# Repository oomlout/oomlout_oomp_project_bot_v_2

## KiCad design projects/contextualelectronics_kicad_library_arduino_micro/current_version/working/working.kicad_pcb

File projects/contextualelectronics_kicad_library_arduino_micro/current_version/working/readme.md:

# kicad_library
 
## summary 
* id: contextualelectronics_kicad_library_arduino_micro
* user: contextualelectronics
* name: kicad_library
* board: arduino_micro
* repo: https://github.com/ContextualElectronics/kicad-library
* src_file_repo_kicad_pcb: template/Arduino_Micro/Arduino_Micro.kicad_pcb
* src_file_repo_kicad_pcb_link: https://github.com/ContextualElectronics/kicad-library/tree/master/template/Arduino_Micro/Arduino_Micro.kicad_pcb

* src_file_repo_sch: template/Arduino_Micro/Arduino_Micro.sch
* src_file_repo_sch_link: https://github.com/ContextualElectronics/kicad-library/tree/master/template/Arduino_Micro/Arduino_Micro.sch
* full details link: https://github.com/oomlout/oomlout_oomp_project_bot_v_2/tree/main/projects/contextualelectronics_kicad_library_arduino_micro/current_version/working  

## schematic  
  
[schematic (pdf)](working_schematic.pdf) 

## pcb  

[board (pdf)](working.pdf)  

## working_bom
| Id | Designator | Footprint | Quantity | Designation | Supplier and ref |  | None | 
| --- | --- | --- | --- | --- | --- | --- | --- | 
| 1 | P1 | Socket_Strip_Arduino_1x17 | 1 | Digital |  |  | [''] | 
| 2 | P2 | Socket_Strip_Arduino_1x17 | 1 | Analog |  |  | [''] | 
| 3 | P3,P4,P5,P6 | 1pin_Micro | 4 | CONN_1 |  |  | [''] | 

## bom_schematic
| Ref | Qnty | Value | Cmp name | Footprint | Description | Vendor | DNP | 
| --- | --- | --- | --- | --- | --- | --- | --- | 
| P1 | 1 | Digital | CONN_17 | Socket_Arduino_Micro:Socket_Strip_Arduino_1x17 |  |  |  | 
| P2 | 1 | Analog | CONN_17 | Socket_Arduino_Micro:Socket_Strip_Arduino_1x17 |  |  |  | 
| P3, P4, P5, P6 | 4 | CONN_1 | CONN_1 | Socket_Arduino_Micro:1pin_Micro |  |  |  |

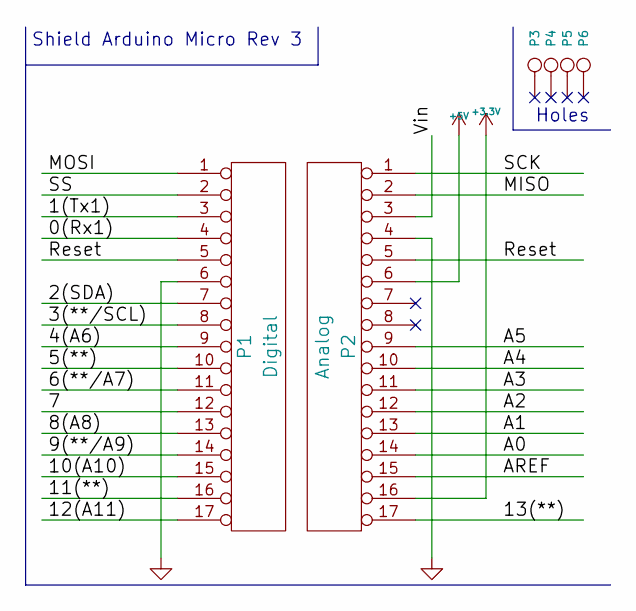
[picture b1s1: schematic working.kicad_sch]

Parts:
P1: Digital; Socket_Strip_Arduino_1x17
P2: Analog; Socket_Strip_Arduino_1x17
P3, P4, P5, P6: CONN_1; 1pin_Micro

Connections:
+3V3: P2.16
+5V: P2.6
/0(Rx1): P1.4
/1(Tx1): P1.3
/2(SDA): P1.7
/3(**/SCL): P1.8
/4(A6): P1.9
/5(**): P1.10
/6(**/A7): P1.11
/7: P1.12
/8(A8): P1.13
/9(**/A9): P1.14
/10(A10): P1.15
/11(**): P1.16
/12(A11): P1.17
/13(**): P2.17
/A0: P2.14
/A1: P2.13
/A2: P2.12
/A3: P2.11
/A4: P2.10
/A5: P2.9
/AREF: P2.15
/MISO: P2.2
/MOSI: P1.1
/Reset: P1.5, P2.5
/SCK: P2.1
/SS: P1.2
/Vin: P2.3
GND: P1.6, P2.4

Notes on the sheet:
Holes
Shield Arduino Micro Rev 3

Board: 2 copper layers, 6 parts (0 on the bottom side), 2 nets, no tracks yet.

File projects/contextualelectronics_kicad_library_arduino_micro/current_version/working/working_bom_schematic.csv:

"Source:","C:\gh\oomlout_oomp_project_bot_v_2\projects\contextualelectronics_kicad_library_arduino_micro\current_version\working\working.kicad_sch"
"Date:","19/09/2023 23:04:57"
"Tool:","Eeschema 7.0.6"
"Generator:","C:/Program Files/KiCad/7.0/bin/scripting/plugins/bom_csv_grouped_by_value_with_fp.py"
"Component Count:","6"
"Ref","Qnty","Value","Cmp name","Footprint","Description","Vendor","DNP"
"P1","1","Digital","CONN_17","Socket_Arduino_Micro:Socket_Strip_Arduino_1x17","","",""
"P2","1","Analog","CONN_17","Socket_Arduino_Micro:Socket_Strip_Arduino_1x17","","",""
"P3, P4, P5, P6","4","CONN_1","CONN_1","Socket_Arduino_Micro:1pin_Micro","","",""

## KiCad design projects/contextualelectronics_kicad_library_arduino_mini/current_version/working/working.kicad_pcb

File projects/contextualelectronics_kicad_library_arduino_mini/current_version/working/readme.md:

# kicad_library
 
## summary 
* id: contextualelectronics_kicad_library_arduino_mini
* user: contextualelectronics
* name: kicad_library
* board: arduino_mini
* repo: https://github.com/ContextualElectronics/kicad-library
* src_file_repo_kicad_pcb: template/Arduino_Mini/Arduino_Mini.kicad_pcb
* src_file_repo_kicad_pcb_link: https://github.com/ContextualElectronics/kicad-library/tree/master/template/Arduino_Mini/Arduino_Mini.kicad_pcb

* src_file_repo_sch: template/Arduino_Mini/Arduino_Mini.sch
* src_file_repo_sch_link: https://github.com/ContextualElectronics/kicad-library/tree/master/template/Arduino_Mini/Arduino_Mini.sch
* full details link: https://github.com/oomlout/oomlout_oomp_project_bot_v_2/tree/main/projects/contextualelectronics_kicad_library_arduino_mini/current_version/working  

## schematic  
  
[schematic (pdf)](working_schematic.pdf) 

## pcb  

[board (pdf)](working.pdf)  

## working_bom
| Id | Designator | Footprint | Quantity | Designation | Supplier and ref |  | None | 
| --- | --- | --- | --- | --- | --- | --- | --- | 
| 1 | P2 | Socket_Strip_Arduino_1x12 | 1 | Digital |  |  | [''] | 
| 2 | P4 | Socket_Strip_Arduino_1x05 | 1 | COM |  |  | [''] | 
| 3 | P5 | Socket_Strip_Arduino_1x12 | 1 | Analog |  |  | [''] | 
| 4 | P1,P3 | Socket_Strip_Arduino_1x02 | 2 | ADC |  |  | [''] | 
| 5 | P6 | Socket_Strip_Arduino_1x02 | 1 | PWR |  |  | [''] | 

## bom_schematic
| Ref | Qnty | Value | Cmp name | Footprint | Description | Vendor | DNP | 
| --- | --- | --- | --- | --- | --- | --- | --- | 
| P1, P3 | 2 | ADC | CONN_2 | Socket_Arduino_Mini:Socket_Strip_Arduino_1x02 |  |  |  | 
| P2 | 1 | Digital | CONN_12 | Socket_Arduino_Mini:Socket_Strip_Arduino_1x12 |  |  |  | 
| P4 | 1 | COM | CONN_5 | Socket_Arduino_Mini:Socket_Strip_Arduino_1x05 |  |  |  | 
| P5 | 1 | Analog | CONN_12 | Socket_Arduino_Mini:Socket_Strip_Arduino_1x12 |  |  |  | 
| P6 | 1 | PWR | CONN_2 | Socket_Arduino_Mini:Socket_Strip_Arduino_1x02 |  |  |  |

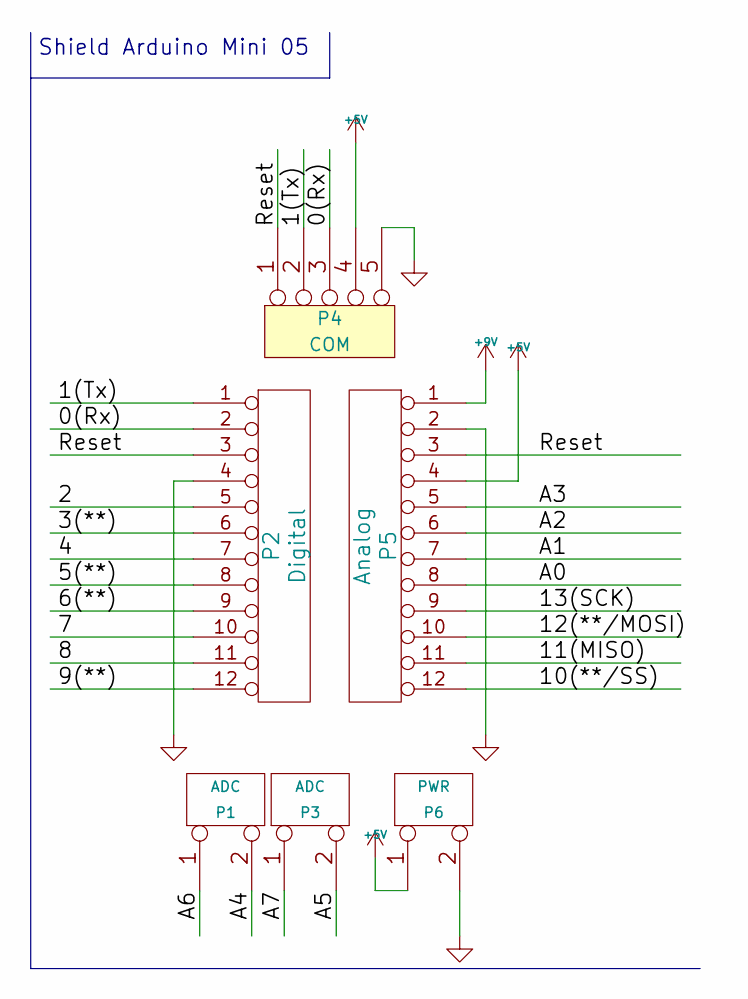
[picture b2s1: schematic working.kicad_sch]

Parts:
P1, P3: ADC; Socket_Strip_Arduino_1x02
P2: Digital; Socket_Strip_Arduino_1x12
P4: COM; Socket_Strip_Arduino_1x05
P5: Analog; Socket_Strip_Arduino_1x12
P6: PWR; Socket_Strip_Arduino_1x02

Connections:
+5V: P4.4, P5.4, P6.1
+9V: P5.1
/0(Rx): P2.2, P4.3
/1(Tx): P2.1, P4.2
/2: P2.5
/3(**): P2.6
/4: P2.7
/5(**): P2.8
/6(**): P2.9
/7: P2.10
/8: P2.11
/9(**): P2.12
/10(**/SS): P5.12
/11(MISO): P5.11
/12(**/MOSI): P5.10
/13(SCK): P5.9
/A0: P5.8
/A1: P5.7
/A2: P5.6
/A3: P5.5
/A4: P1.2 (PM)
/A5: P3.2 (PM)
/A6: P1.1
/A7: P3.1
/Reset: P2.3, P4.1, P5.3
GND: P2.4, P4.5, P5.2, P6.2 (PM)

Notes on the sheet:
Shield Arduino Mini 05

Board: 2 copper layers, 6 parts (0 on the bottom side), 5 nets, no tracks yet.

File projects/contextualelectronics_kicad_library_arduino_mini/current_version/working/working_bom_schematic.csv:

"Source:","C:\gh\oomlout_oomp_project_bot_v_2\projects\contextualelectronics_kicad_library_arduino_mini\current_version\working\working.kicad_sch"
"Date:","19/09/2023 23:12:36"
"Tool:","Eeschema 7.0.6"
"Generator:","C:/Program Files/KiCad/7.0/bin/scripting/plugins/bom_csv_grouped_by_value_with_fp.py"
"Component Count:","6"
"Ref","Qnty","Value","Cmp name","Footprint","Description","Vendor","DNP"
"P1, P3","2","ADC","CONN_2","Socket_Arduino_Mini:Socket_Strip_Arduino_1x02","","",""
"P2","1","Digital","CONN_12","Socket_Arduino_Mini:Socket_Strip_Arduino_1x12","","",""
"P4","1","COM","CONN_5","Socket_Arduino_Mini:Socket_Strip_Arduino_1x05","","",""
"P5","1","Analog","CONN_12","Socket_Arduino_Mini:Socket_Strip_Arduino_1x12","","",""
"P6","1","PWR","CONN_2","Socket_Arduino_Mini:Socket_Strip_Arduino_1x02","","",""

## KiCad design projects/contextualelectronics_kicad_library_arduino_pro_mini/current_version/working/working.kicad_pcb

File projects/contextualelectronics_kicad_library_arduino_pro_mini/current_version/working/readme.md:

# kicad_library
 
## summary 
* id: contextualelectronics_kicad_library_arduino_pro_mini
* user: contextualelectronics
* name: kicad_library
* board: arduino_pro_mini
* repo: https://github.com/ContextualElectronics/kicad-library
* src_file_repo_kicad_pcb: template/Arduino_Pro_Mini/Arduino_Pro_Mini.kicad_pcb
* src_file_repo_kicad_pcb_link: https://github.com/ContextualElectronics/kicad-library/tree/master/template/Arduino_Pro_Mini/Arduino_Pro_Mini.kicad_pcb

* src_file_repo_sch: template/Arduino_Pro_Mini/Arduino_Pro_Mini.sch
* src_file_repo_sch_link: https://github.com/ContextualElectronics/kicad-library/tree/master/template/Arduino_Pro_Mini/Arduino_Pro_Mini.sch
* full details link: https://github.com/oomlout/oomlout_oomp_project_bot_v_2/tree/main/projects/contextualelectronics_kicad_library_arduino_pro_mini/current_version/working  

## schematic  
  
[schematic (pdf)](working_schematic.pdf) 

## pcb  

[board (pdf)](working.pdf)  

## working_bom
| Id | Designator | Footprint | Quantity | Designation | Supplier and ref |  | None | 
| --- | --- | --- | --- | --- | --- | --- | --- | 
| 1 | P1 | Socket_Strip_Arduino_1x12 | 1 | Digital |  |  | [''] | 
| 2 | P2 | Socket_Strip_Arduino_1x06 | 1 | COM |  |  | [''] | 
| 3 | P3,P5 | Socket_Strip_Arduino_1x02 | 2 | ADC |  |  | [''] | 
| 4 | P4 | Socket_Strip_Arduino_1x12 | 1 | Analog |  |  | [''] | 

## bom_schematic
| Ref | Qnty | Value | Cmp name | Footprint | Description | Vendor | DNP | 
| --- | --- | --- | --- | --- | --- | --- | --- | 
| P1 | 1 | Digital | CONN_12 | Socket_Arduino_Pro_Mini:Socket_Strip_Arduino_1x12 |  |  |  | 
| P2 | 1 | COM | CONN_6 | Socket_Arduino_Pro_Mini:Socket_Strip_Arduino_1x06 |  |  |  | 
| P3, P5 | 2 | ADC | CONN_2 | Socket_Arduino_Pro_Mini:Socket_Strip_Arduino_1x02 |  |  |  | 
| P4 | 1 | Analog | CONN_12 | Socket_Arduino_Pro_Mini:Socket_Strip_Arduino_1x12 |  |  |  |

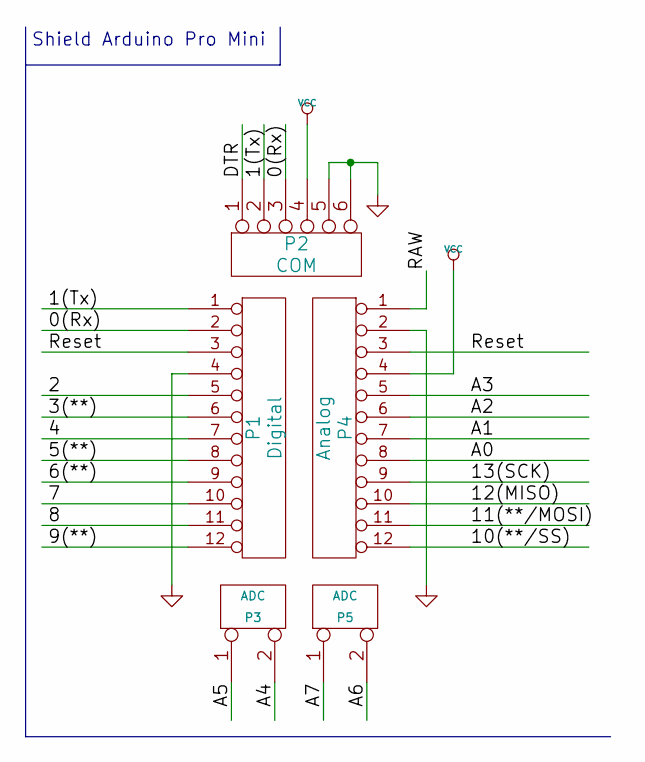
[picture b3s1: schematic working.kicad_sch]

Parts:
P1: Digital; Socket_Strip_Arduino_1x12
P2: COM; Socket_Strip_Arduino_1x06
P3, P5: ADC; Socket_Strip_Arduino_1x02
P4: Analog; Socket_Strip_Arduino_1x12

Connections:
/0(Rx): P1.2, P2.3
/1(Tx): P1.1, P2.2
/2: P1.5
/3(**): P1.6
/4: P1.7
/5(**): P1.8
/6(**): P1.9
/7: P1.10
/8: P1.11
/9(**): P1.12
/10(**/SS): P4.12
/11(**/MOSI): P4.11
/12(MISO): P4.10
/13(SCK): P4.9
/A0: P4.8
/A1: P4.7
/A2: P4.6
/A3: P4.5
/A4: P3.2 (PM)
/A5: P3.1
/A6: P5.2 (PM)
/A7: P5.1
/DTR: P2.1
/RAW: P4.1
/Reset: P1.3, P4.3
GND: P1.4, P2.5, P2.6, P4.2
VCC: P2.4, P4.4

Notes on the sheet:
Shield Arduino Pro Mini

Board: 2 copper layers, 5 parts (0 on the bottom side), 5 nets, no tracks yet.

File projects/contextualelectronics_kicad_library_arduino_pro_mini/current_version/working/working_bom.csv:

"Id";"Designator";"Footprint";"Quantity";"Designation";"Supplier and ref";
1;"P1";"Socket_Strip_Arduino_1x12";1;"Digital";;;
2;"P2";"Socket_Strip_Arduino_1x06";1;"COM";;;
3;"P3,P5";"Socket_Strip_Arduino_1x02";2;"ADC";;;
4;"P4";"Socket_Strip_Arduino_1x12";1;"Analog";;;
